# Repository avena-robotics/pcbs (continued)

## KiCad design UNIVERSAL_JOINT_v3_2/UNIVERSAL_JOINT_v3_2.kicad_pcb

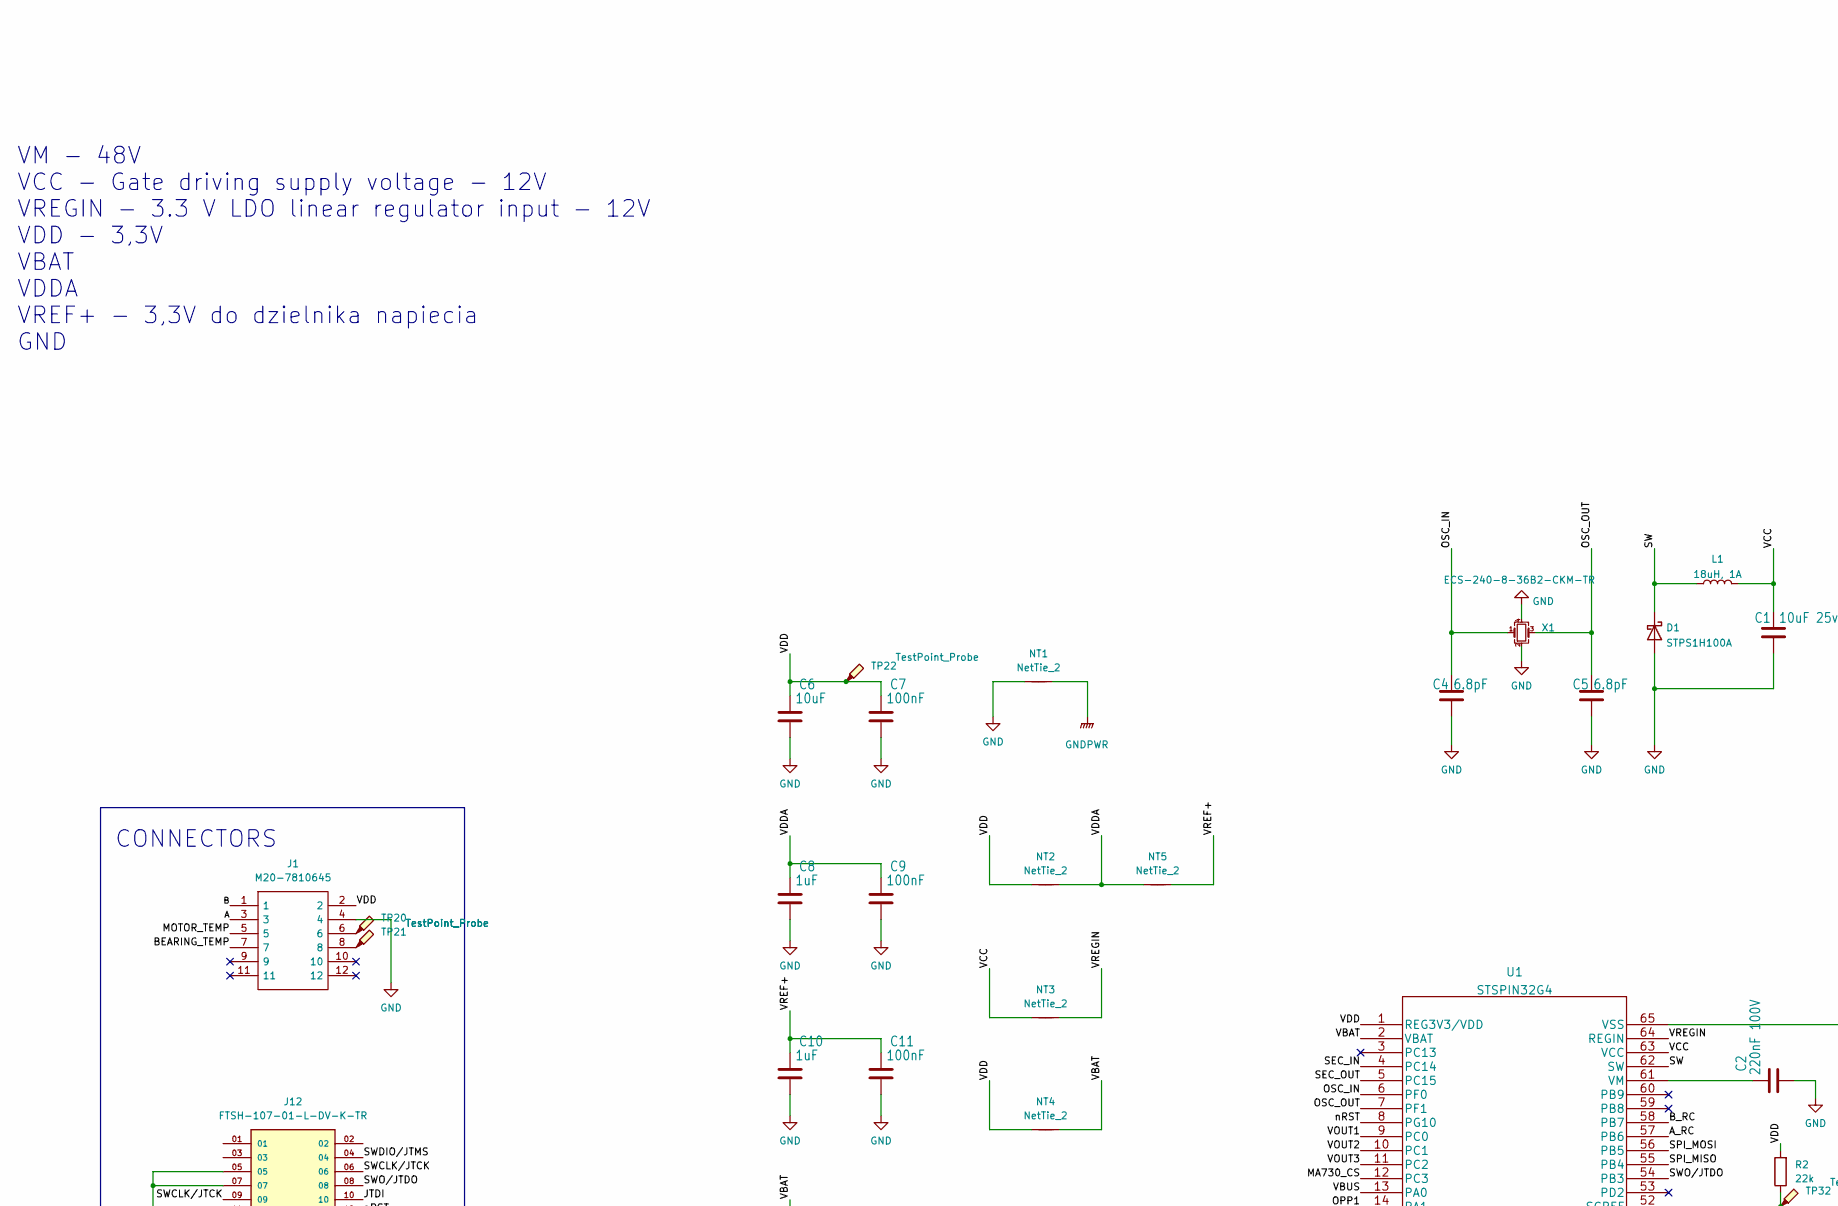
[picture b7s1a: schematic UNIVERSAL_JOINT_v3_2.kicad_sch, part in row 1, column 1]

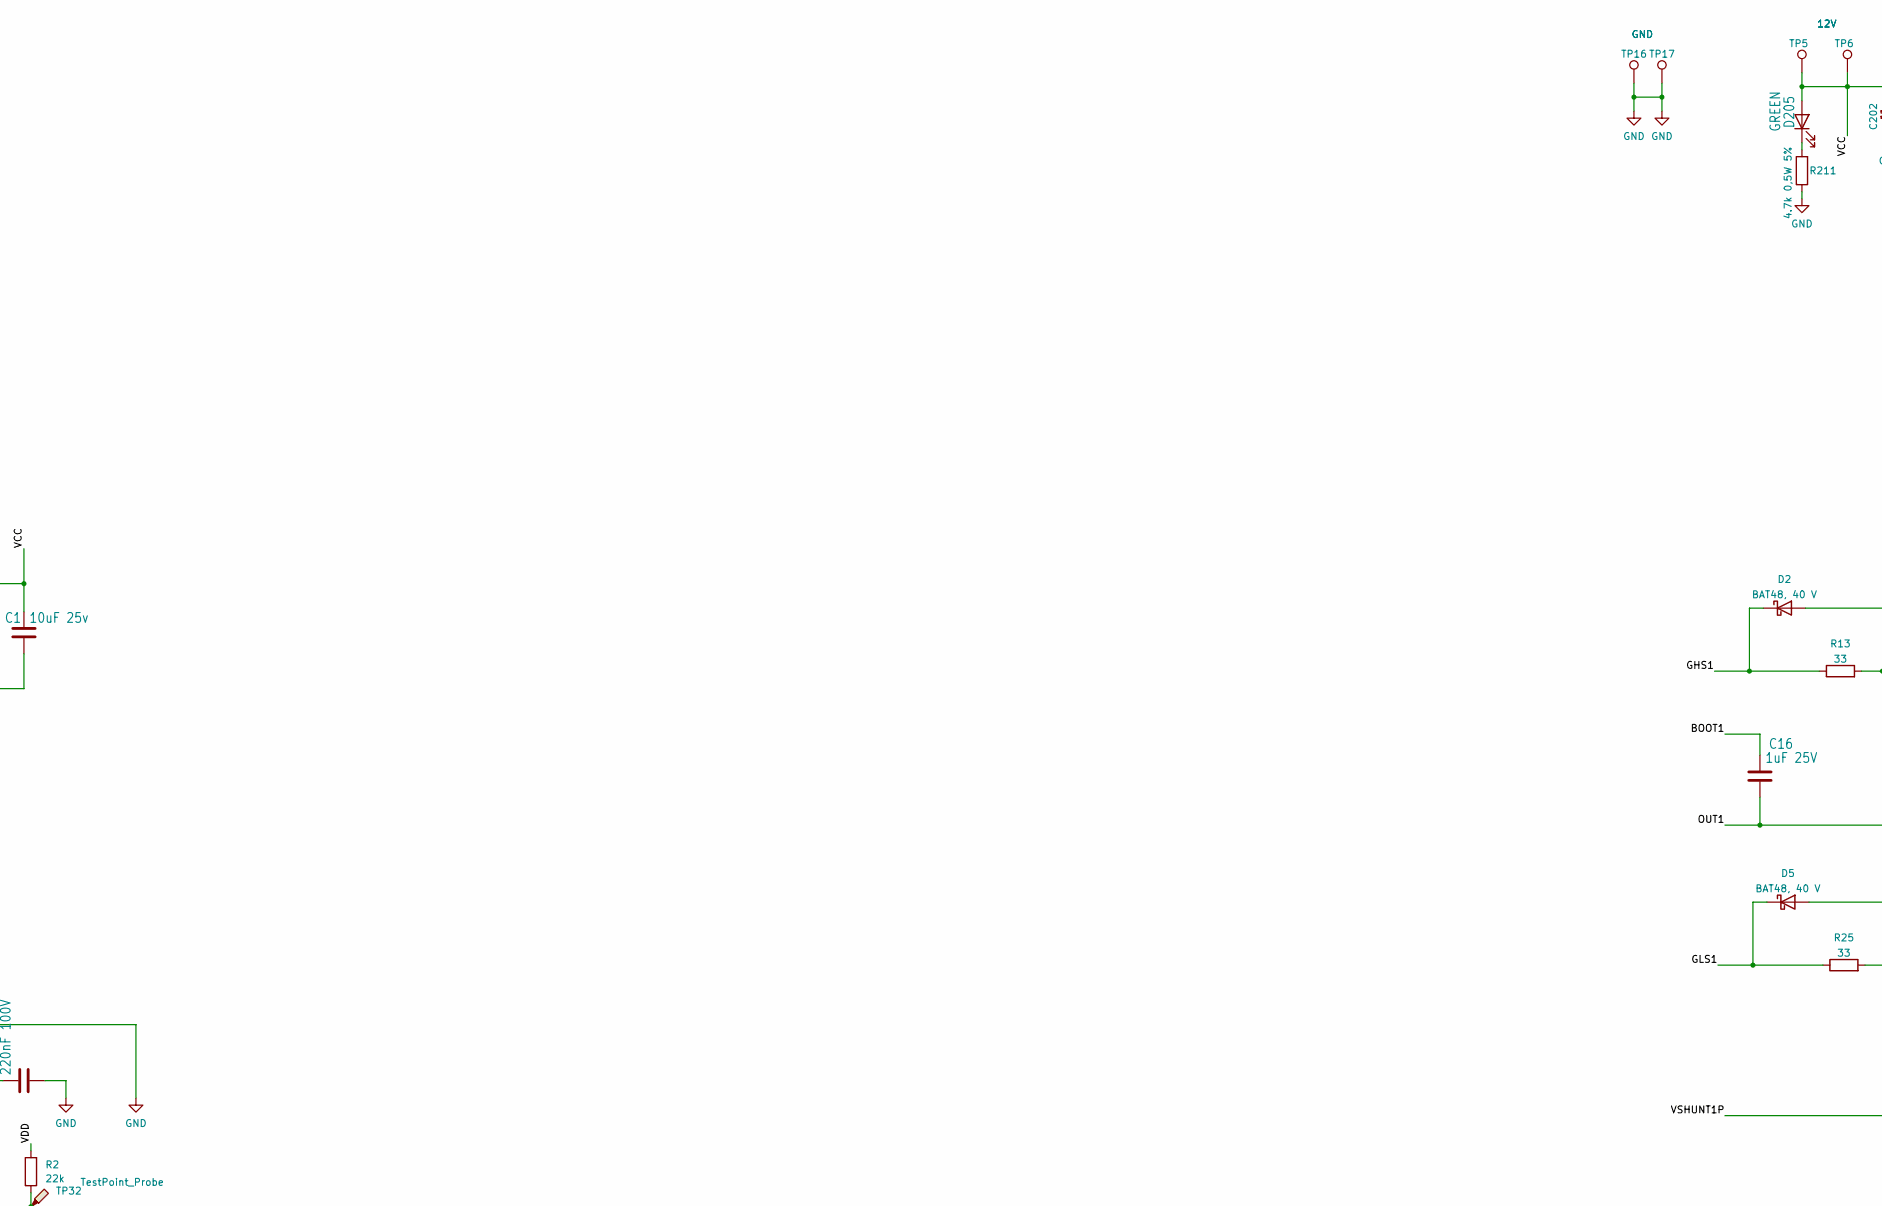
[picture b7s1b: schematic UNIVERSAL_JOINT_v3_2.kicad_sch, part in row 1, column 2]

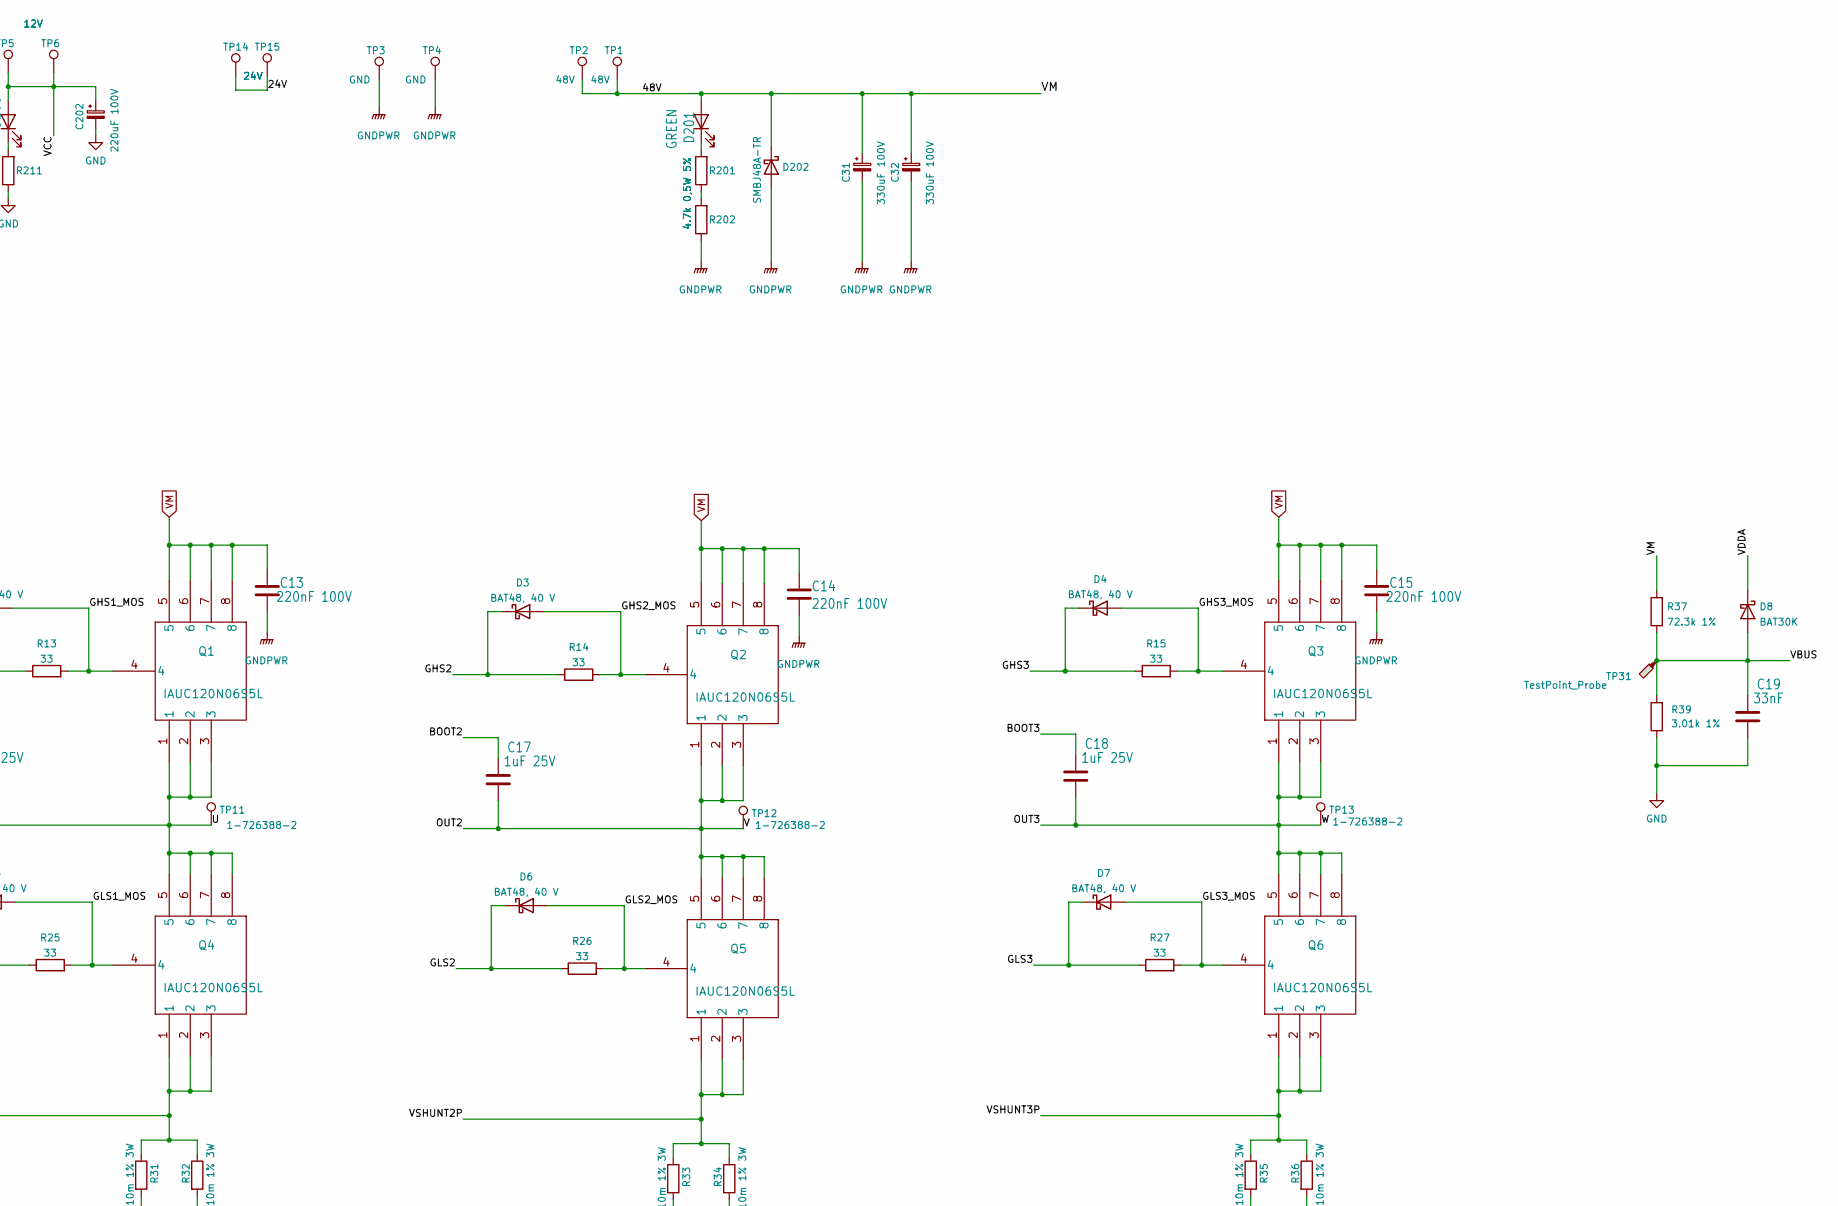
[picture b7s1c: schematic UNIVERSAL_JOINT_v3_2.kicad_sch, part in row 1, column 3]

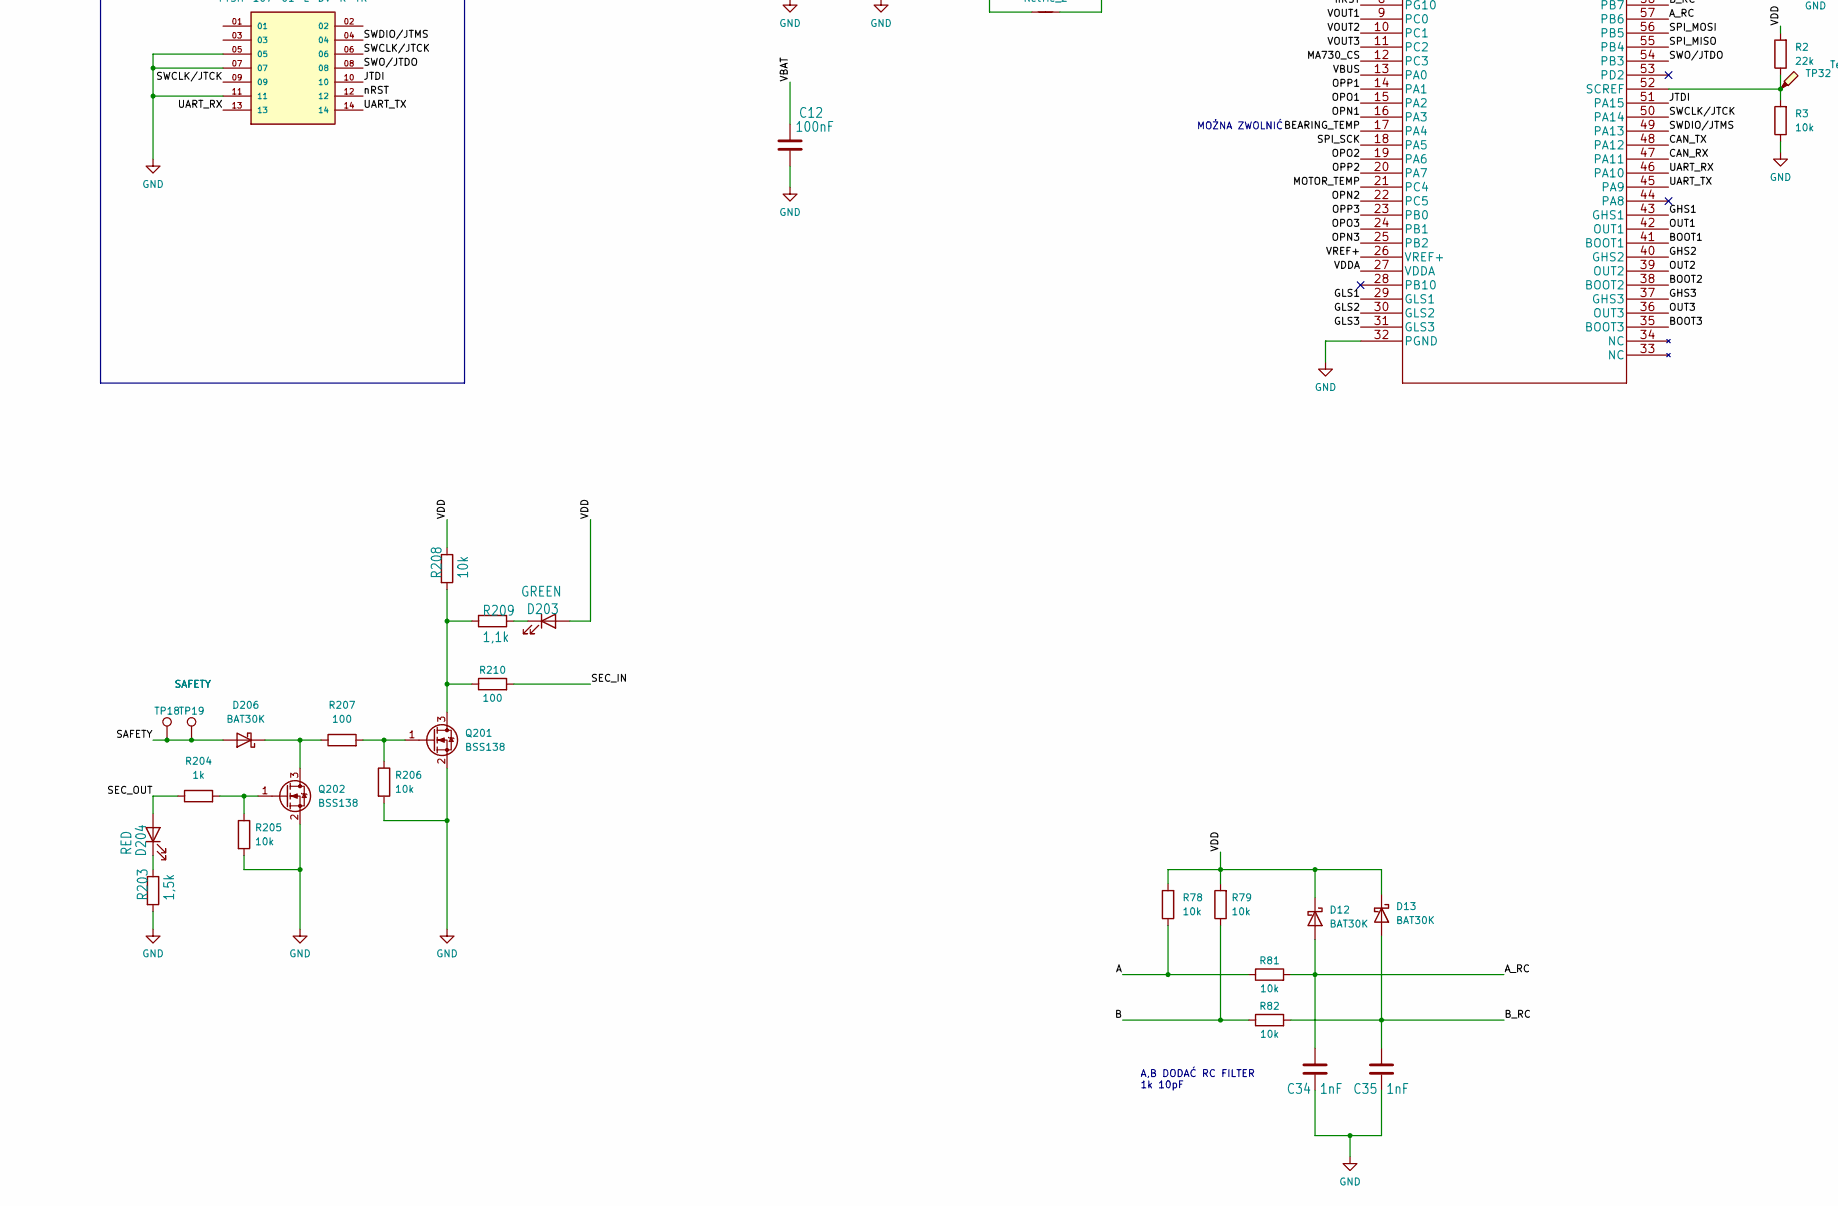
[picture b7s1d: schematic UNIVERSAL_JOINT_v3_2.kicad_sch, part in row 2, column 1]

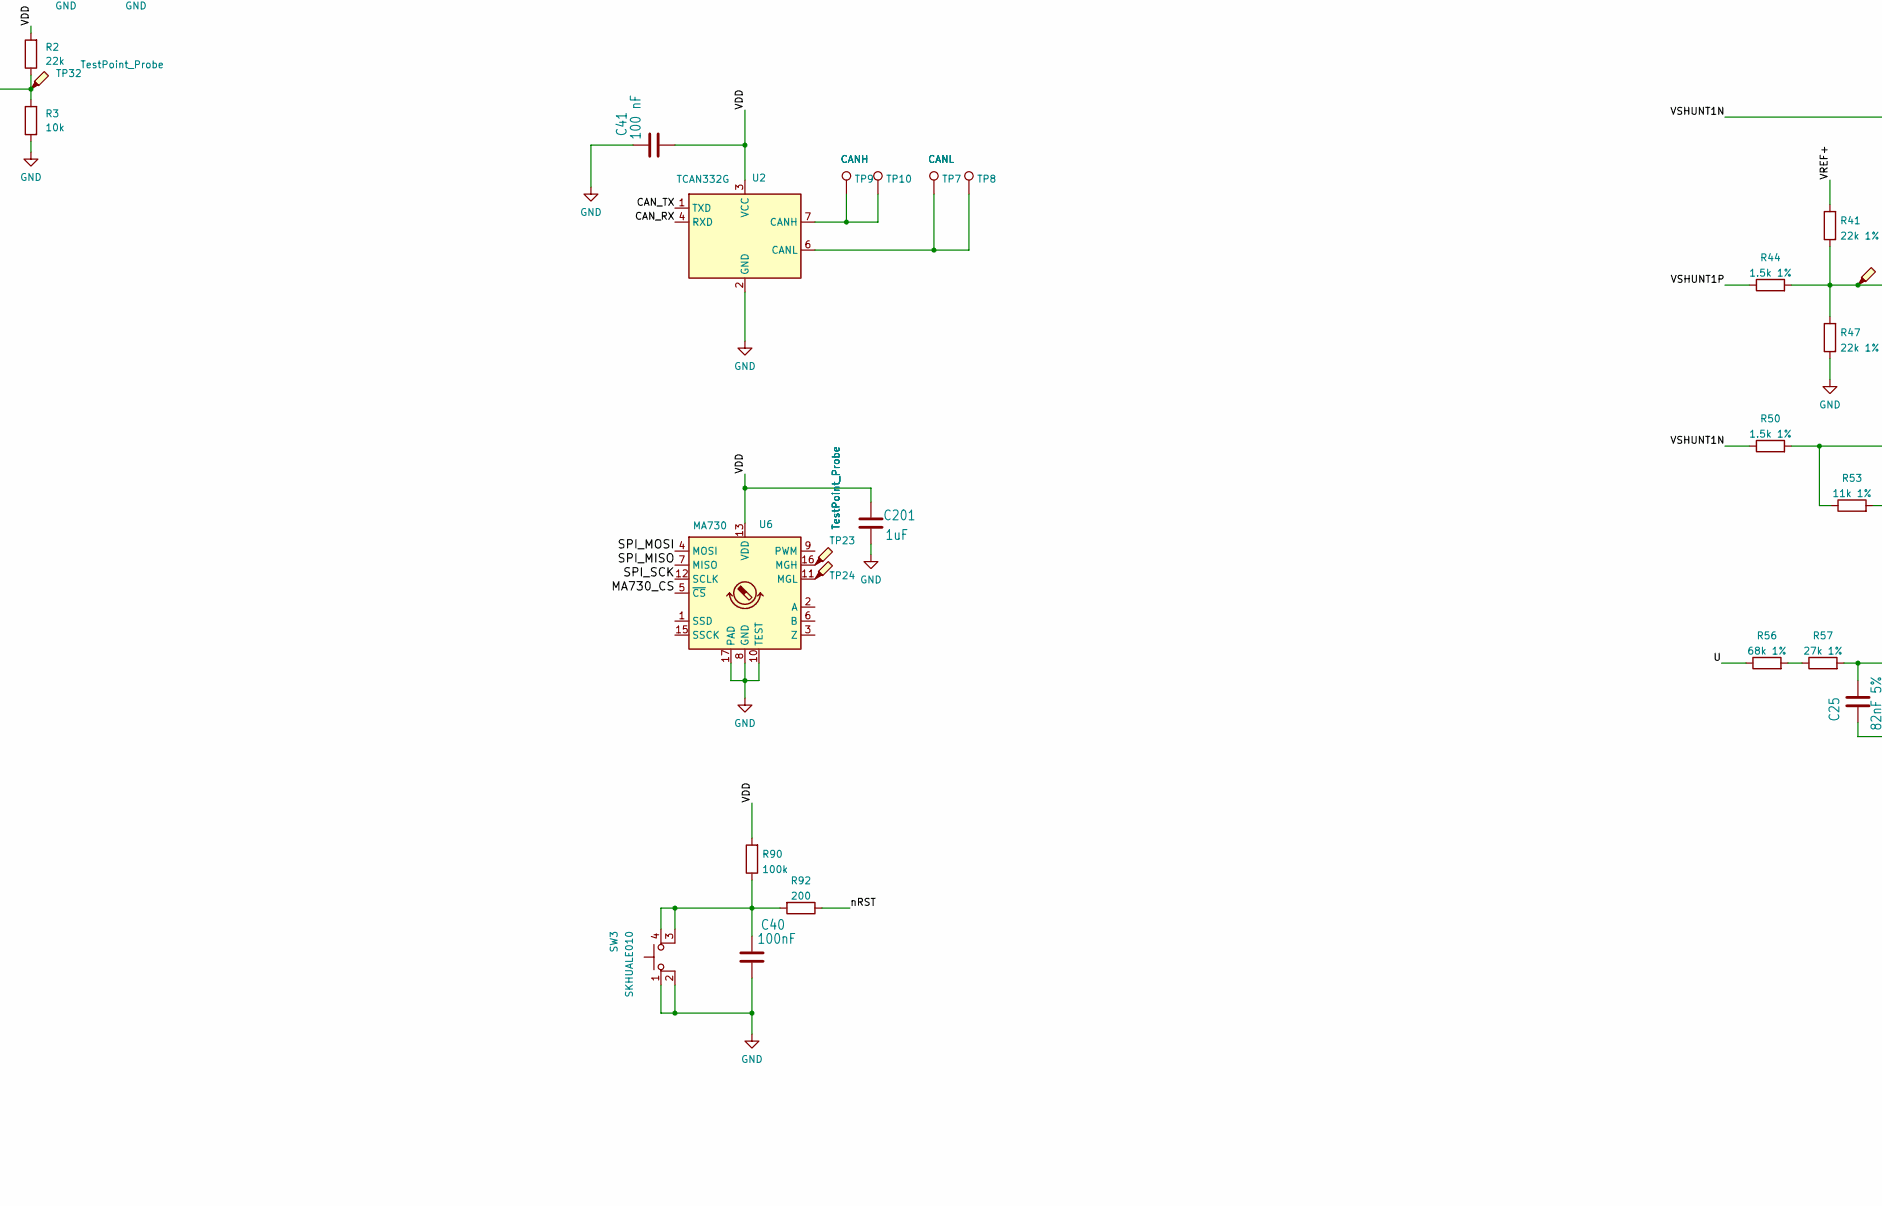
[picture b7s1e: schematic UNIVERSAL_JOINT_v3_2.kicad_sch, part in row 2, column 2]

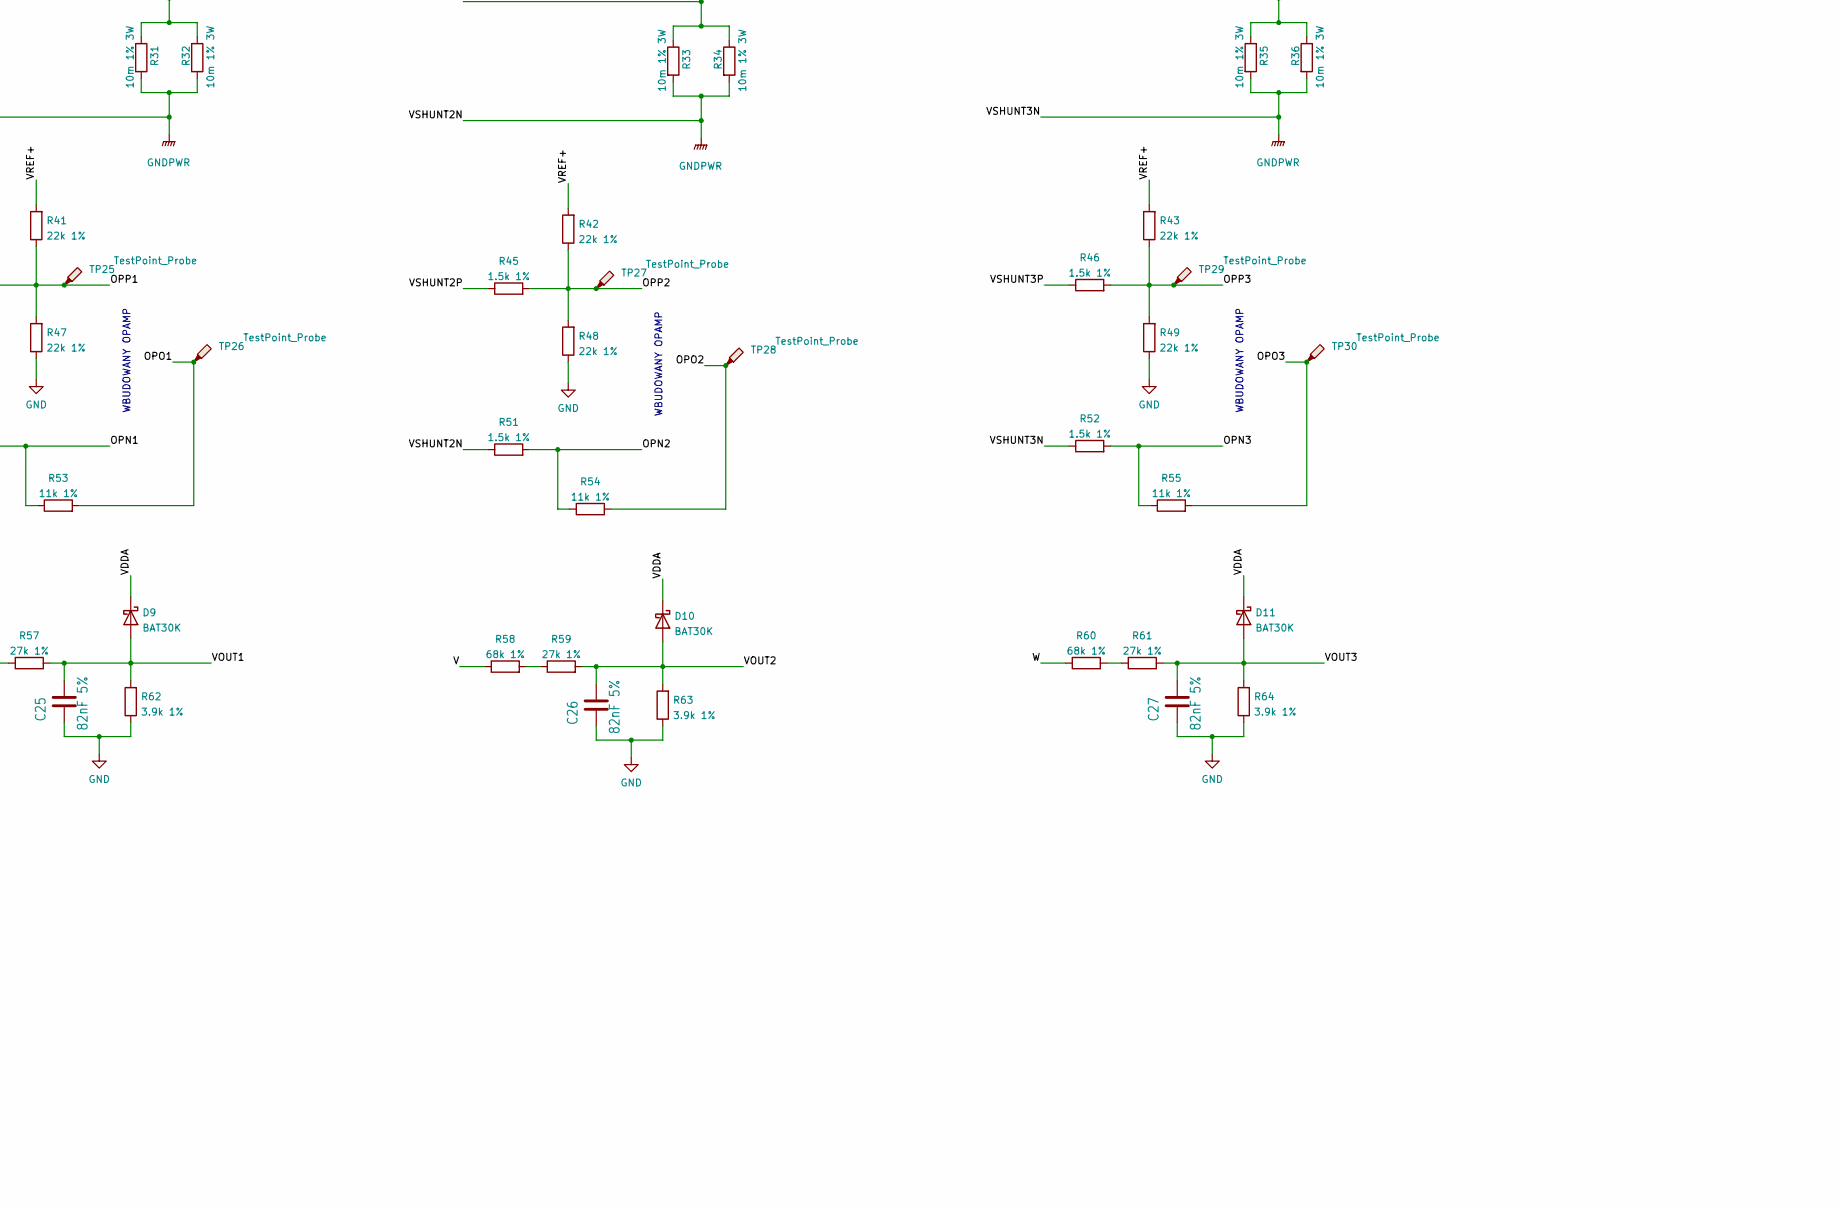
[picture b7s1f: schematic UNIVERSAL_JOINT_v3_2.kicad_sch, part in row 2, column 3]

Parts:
C1: 10uF 25v; C_0603_1608Metric_Pad1.08x0.95mm_HandSolder
C2, C13, C14, C15: 220nF 100V; C_0603_1608Metric_Pad1.08x0.95mm_HandSolder
C4, C5: 6.8pF; C_0603_1608Metric_Pad1.08x0.95mm_HandSolder
C6: 10uF; C_0603_1608Metric_Pad1.08x0.95mm_HandSolder
C7, C9, C11, C12, C40: 100nF; C_0603_1608Metric_Pad1.08x0.95mm_HandSolder
C8, C10, C201: 1uF; C_0603_1608Metric_Pad1.08x0.95mm_HandSolder
C16, C17, C18: 1uF 25V; C_0603_1608Metric_Pad1.08x0.95mm_HandSolder
C19: 33nF; C_0603_1608Metric_Pad1.08x0.95mm_HandSolder
C25, C26, C27: 82nF 5%; C_0603_1608Metric_Pad1.08x0.95mm_HandSolder
C31, C32: 330uF 100V; CP_Radial_D12.5mm_P5.00mm
C34, C35: 1nF; C_0603_1608Metric_Pad1.08x0.95mm_HandSolder
C41: 100 nF; C_0603_1608Metric_Pad1.08x0.95mm_HandSolder
C202: 220uF 100V; CP_Radial_D6.3mm_P2.50mm
D1: STPS1H100A; D_0603_1608Metric_Pad1.05x0.95mm_HandSolder
D2, D3, D4, D5, D6, D7: BAT48, 40 V; D_0603_1608Metric_Pad1.05x0.95mm_HandSolder
D8, D9, D10, D11, D12, D13, D206: BAT30K; D_0603_1608Metric_Pad1.05x0.95mm_HandSolder
D201, D203, D205: GREEN; D_0603_1608Metric_Pad1.05x0.95mm_HandSolder
D202: SMBJ48A-TR; D_0603_1608Metric_Pad1.05x0.95mm_HandSolder
D204: RED; D_0603_1608Metric_Pad1.05x0.95mm_HandSolder
J1: M20-7810645; Mouser Part Number 855-M20-7810645
J12: FTSH-107-01-L-DV-K-TR; SAMTEC_FTSH-107-01-L-DV-K-TR; PARTREV R
L1: 18uH, 1A; L_Wuerth_WE-PD2-Typ-MS
NT1, NT2, NT3, NT4, NT5: NetTie_2; NetTie-2_SMD_Pad0.5mm
Q1, Q2, Q3, Q4, Q5, Q6: IAUC120N06S5L; STL110N10F7
Q201, Q202: BSS138; SOT-23
R2: 22k; R_0603_1608Metric_Pad0.98x0.95mm_HandSolder
R3, R78, R79, R81, R82, R205, R206, R208: 10k; R_0603_1608Metric_Pad0.98x0.95mm_HandSolder
R13, R14, R15, R25, R26, R27: 33; R_0603_1608Metric_Pad0.98x0.95mm_HandSolder
R31, R32, R33, R34, R35, R36: 10m 1% 3W; R_2512_6332Metric_Pad1.40x3.35mm_HandSolder
R37: 72.3k 1%; R_0603_1608Metric_Pad0.98x0.95mm_HandSolder
R39: 3.01k 1%; R_0603_1608Metric_Pad0.98x0.95mm_HandSolder
R41, R42, R43, R47, R48, R49: 22k 1%; R_0603_1608Metric_Pad0.98x0.95mm_HandSolder
R44, R45, R46, R50, R51, R52: 1.5k 1%; R_0603_1608Metric_Pad0.98x0.95mm_HandSolder
R53, R54, R55: 11k 1%; R_0603_1608Metric_Pad0.98x0.95mm_HandSolder
R56, R58, R60: 68k 1%; R_0603_1608Metric_Pad0.98x0.95mm_HandSolder
R57, R59, R61: 27k 1%; R_0603_1608Metric_Pad0.98x0.95mm_HandSolder
R62, R63, R64: 3.9k 1%; R_0603_1608Metric_Pad0.98x0.95mm_HandSolder
R90: 100k; R_0603_1608Metric_Pad0.98x0.95mm_HandSolder
R92: 200; R_0603_1608Metric_Pad0.98x0.95mm_HandSolder
R201, R202, R211: 4.7k 0,5W 5%; R_0603_1608Metric_Pad0.98x0.95mm_HandSolder
R203: 1,5k; R_0603_1608Metric_Pad0.98x0.95mm_HandSolder
R204: 1k; R_0603_1608Metric_Pad0.98x0.95mm_HandSolder
R207, R210: 100; R_0603_1608Metric_Pad0.98x0.95mm_HandSolder
R209: 1,1k; R_0603_1608Metric_Pad0.98x0.95mm_HandSolder
SW3: SKHUALE010
TP1, TP2: 48V; 1-726388-2
TP3, TP4: GND; 1-726388-2
TP5, TP6: 12V; 61-2348-11_0030
TP7, TP8: CANL; KEYS_3544
TP9, TP10: CANH; 61-2348-11_0030
TP11, TP12, TP13: 1-726388-2; 61-2348-11_0030
TP14, TP15: 24V; KEYS_3578
TP16, TP17: GND; 61-2348-11_0030
TP18, TP19: SAFETY; KEYS_3544
TP20, TP21, TP22, TP23, TP24, TP25, TP26, TP27, TP28, TP29, TP30, TP31, TP32: TestPoint_Probe; TestPoint_Pad_D1.0mm
U1: STSPIN32G4
U2: TCAN332G; SO-8_3.9x4.9mm_P1.27mm
U6: MA730; MA730GQ-Z
X1: ECS-240-8-36B2-CKM-TR; ECX-2236B2

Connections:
/24V: TP14.1, TP15.1
/A: J1.3, R78.1, R81.1
/A_RC: C34.1, D12.2 (A), R81.2, U1.57 (PB6)
/B: J1.1, R79.1, R82.1
/BEARING_TEMP: J1.7, U1.17 (PA4)
/BOOT1: C16.2, U1.41 (BOOT1)
/BOOT2: C17.2, U1.38 (BOOT2)
/BOOT3: C18.2, U1.35 (BOOT3)
/B_RC: C35.1, D13.2 (A), R82.2, U1.58 (PB7)
/CAN_RX: U1.47 (PA11), U2.4 (RXD)
/CAN_TX: U1.48 (PA12), U2.1 (TXD)
/GHS1: D2.1 (K), R13.1, U1.43 (GHS1)
/GHS1_MOS: D2.2 (A), Q1.4, R13.2
/GHS2: D3.1 (K), R14.1, U1.40 (GHS2)
/GHS2_MOS: D3.2 (A), Q2.4, R14.2
/GHS3: D4.1 (K), R15.1, U1.37 (GHS3)
/GHS3_MOS: D4.2 (A), Q3.4, R15.2
/GLS1: D5.1 (K), R25.1, U1.29 (GLS1)
/GLS1_MOS: D5.2 (A), Q4.4, R25.2
/GLS2: D6.1 (K), R26.1, U1.30 (GLS2)
/GLS2_MOS: D6.2 (A), Q5.4, R26.2
/GLS3: D7.1 (K), R27.1, U1.31 (GLS3)
/GLS3_MOS: D7.2 (A), Q6.4, R27.2
/JTDI: J12.10, U1.51 (PA15)
/MA730_CS: U1.12 (PC3), U6.5 (~CS)
/MOTOR_TEMP: J1.5, U1.21 (PC4)
/OPN1: R50.2, R53.1, U1.16 (PA3)
/OPN2: R51.2, R54.1, U1.22 (PC5)
/OPN3: R52.2, R55.1, U1.25 (PB2)
/OPO1: R53.2, TP26.1, U1.15 (PA2)
/OPO2: R54.2, TP28.1, U1.19 (PA6)
/OPO3: R55.2, TP30.1, U1.24 (PB1)
/OPP1: R41.1, R44.2, R47.2, TP25.1, U1.14 (PA1)
/OPP2: R42.1, R45.2, R48.2, TP27.1, U1.20 (PA7)
/OPP3: R43.1, R46.2, R49.2, TP29.1, U1.23 (PB0)
/OSC_IN: C4.2, U1.6 (PF0), X1.1
/OSC_OUT: C5.2, U1.7 (PF1), X1.3
/OUT1: C16.1, Q1.1, Q1.2, Q1.3, Q4.5, Q4.6, Q4.7, Q4.8, R56.1, TP11.1, U1.42 (OUT1)
/OUT2: C17.1, Q2.1, Q2.2, Q2.3, Q5.5, Q5.6, Q5.7, Q5.8, R58.1, TP12.1, U1.39 (OUT2)
/OUT3: C18.1, Q3.1, Q3.2, Q3.3, Q6.5, Q6.6, Q6.7, Q6.8, R60.1, TP13.1, U1.36 (OUT3)
/SAFETY: D206.2 (A), TP18.1, TP19.1
/SEC_IN: R210.2, U1.4 (PC14)
/SEC_OUT: D204.2 (A), R204.1, U1.5 (PC15)
/SPI_MISO: U1.55 (PB4), U6.7 (MISO)
/SPI_MOSI: U1.56 (PB5), U6.4 (MOSI)
/SPI_SCK: U1.18 (PA5), U6.12 (SCLK)
/SW: D1.1 (K), L1.1, U1.62 (SW)
/SWCLK/JTCK: J12.06, J12.09, U1.50 (PA14)
/SWDIO/JTMS: J12.04, U1.49 (PA13)
/SWO/JTDO: J12.08, U1.54 (PB3)
/UART_RX: J12.13, U1.46 (PA10)
/UART_TX: J12.14, U1.45 (PA9)
/VBAT: C12.2, NT4.2, U1.2 (VBAT)
/VBUS: C19.2, D8.2 (A), R37.1, R39.2, TP31.1, U1.13 (PA0)
/VCC: C1.2, C202.1, D205.2 (A), L1.2, NT3.1, TP5.1, TP6.1, U1.63 (VCC)
/VDD: C6.2, C7.2, C41.1, C201.2, D12.1 (K), D13.1 (K), D203.2 (A), J1.2, NT2.1, NT4.1, R2.2, R78.2, R79.2, R90.2, R208.1, TP22.1, U1.1 (REG3V3/VDD), U2.3 (VCC), U6.13 (VDD)
/VDDA: C8.2, C9.2, D8.1 (K), D9.1 (K), D10.1 (K), D11.1 (K), NT2.2, NT5.1, U1.27 (VDDA)
/VOUT1: C25.1, D9.2 (A), R57.2, R62.2, U1.9 (PC0)
/VOUT2: C26.1, D10.2 (A), R59.2, R63.2, U1.10 (PC1)
/VOUT3: C27.1, D11.2 (A), R61.2, R64.2, U1.11 (PC2)
/VREF+: C10.2, C11.2, NT5.2, R41.2, R42.2, R43.2, U1.26 (VREF+)
/VREGIN: NT3.2, U1.64 (REGIN)
/VSHUNT1P: Q4.1, Q4.2, Q4.3, R31.1, R32.1, R44.1
/VSHUNT2P: Q5.1, Q5.2, Q5.3, R33.1, R34.1, R45.1
/VSHUNT3P: Q6.1, Q6.2, Q6.3, R35.1, R36.1, R46.1
/nRST: J12.12, R92.1, U1.8 (PG10)
GND: C1.1, C2.1, C4.1, C5.1, C6.1, C7.1, C8.1, C9.1, C10.1, C11.1, C12.1, C19.1, C25.2, C26.2, C27.2, C34.2, C35.2, C40.1, C41.2, C201.1, C202.2, D1.2 (A), J1.4, J12.05, J12.07, J12.11, NT1.1, Q201.2 (S), Q202.2 (S), R3.1, R39.1, R47.1, R48.1, R49.1, R62.1, R63.1, R64.1, R203.2, R205.2, R206.2, R211.1, SW3.1, SW3.2, TP16.1, TP17.1, U1.32 (PGND), U1.65 (VSS), U2.2 (GND), U6.8 (GND), U6.10 (TEST), U6.17 (PAD), X1.2, X1.4
GNDPWR: C13.1, C14.1, C15.1, C31.2, C32.2, D202.2 (A), NT1.2, R31.2, R32.2, R33.2, R34.2, R35.2, R36.2, R50.1, R51.1, R52.1, R202.1, TP3.1, TP4.1
unnamed: C2.2, U1.61 (VM)
unnamed: C40.2, R90.1, R92.2, SW3.3 (K), SW3.4 (A)
unnamed: D201.1 (K), R201.2
unnamed: D203.1 (K), R209.1
unnamed: D204.1 (K), R203.1
unnamed: D205.1 (K), R211.2
unnamed: D206.1 (K), Q202.3 (D), R207.1
unnamed: J1.6, TP20.1
unnamed: J1.8, TP21.1
unnamed: Q201.1 (G), R206.1, R207.2
unnamed: Q201.3 (D), R208.2, R209.2, R210.1
unnamed: Q202.1 (G), R204.2, R205.1
unnamed: R2.1, R3.2, TP32.1, U1.52 (SCREF)
unnamed: R56.2, R57.1
unnamed: R58.2, R59.1
unnamed: R60.2, R61.1
unnamed: R201.1, R202.2
unnamed: TP7.1, TP8.1, U2.6 (CANL)
unnamed: TP9.1, TP10.1, U2.7 (CANH)
unnamed: TP23.1, U6.16 (MGH)
unnamed: TP24.1, U6.11 (MGL)
VM: C13.2, C14.2, C15.2, C31.1, C32.1, D201.2 (A), D202.1 (K), Q1.5, Q1.6, Q1.7, Q1.8, Q2.5, Q2.6, Q2.7, Q2.8, Q3.5, Q3.6, Q3.7, Q3.8, R37.2, TP1.1, TP2.1

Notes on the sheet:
VM - 48V VCC - Gate driving supply voltage - 12V VREGIN - 3.3 V LDO linear regulator input - 12V VDD - 3,3V VBAT VDDA VREF+ - 3,3V do dzielnika napiecia GND
CONNECTORS
WBUDOWANY OPAMP
A,B DODAĆ RC FILTER 1k 10pF
MOŻNA ZWOLNIĆ

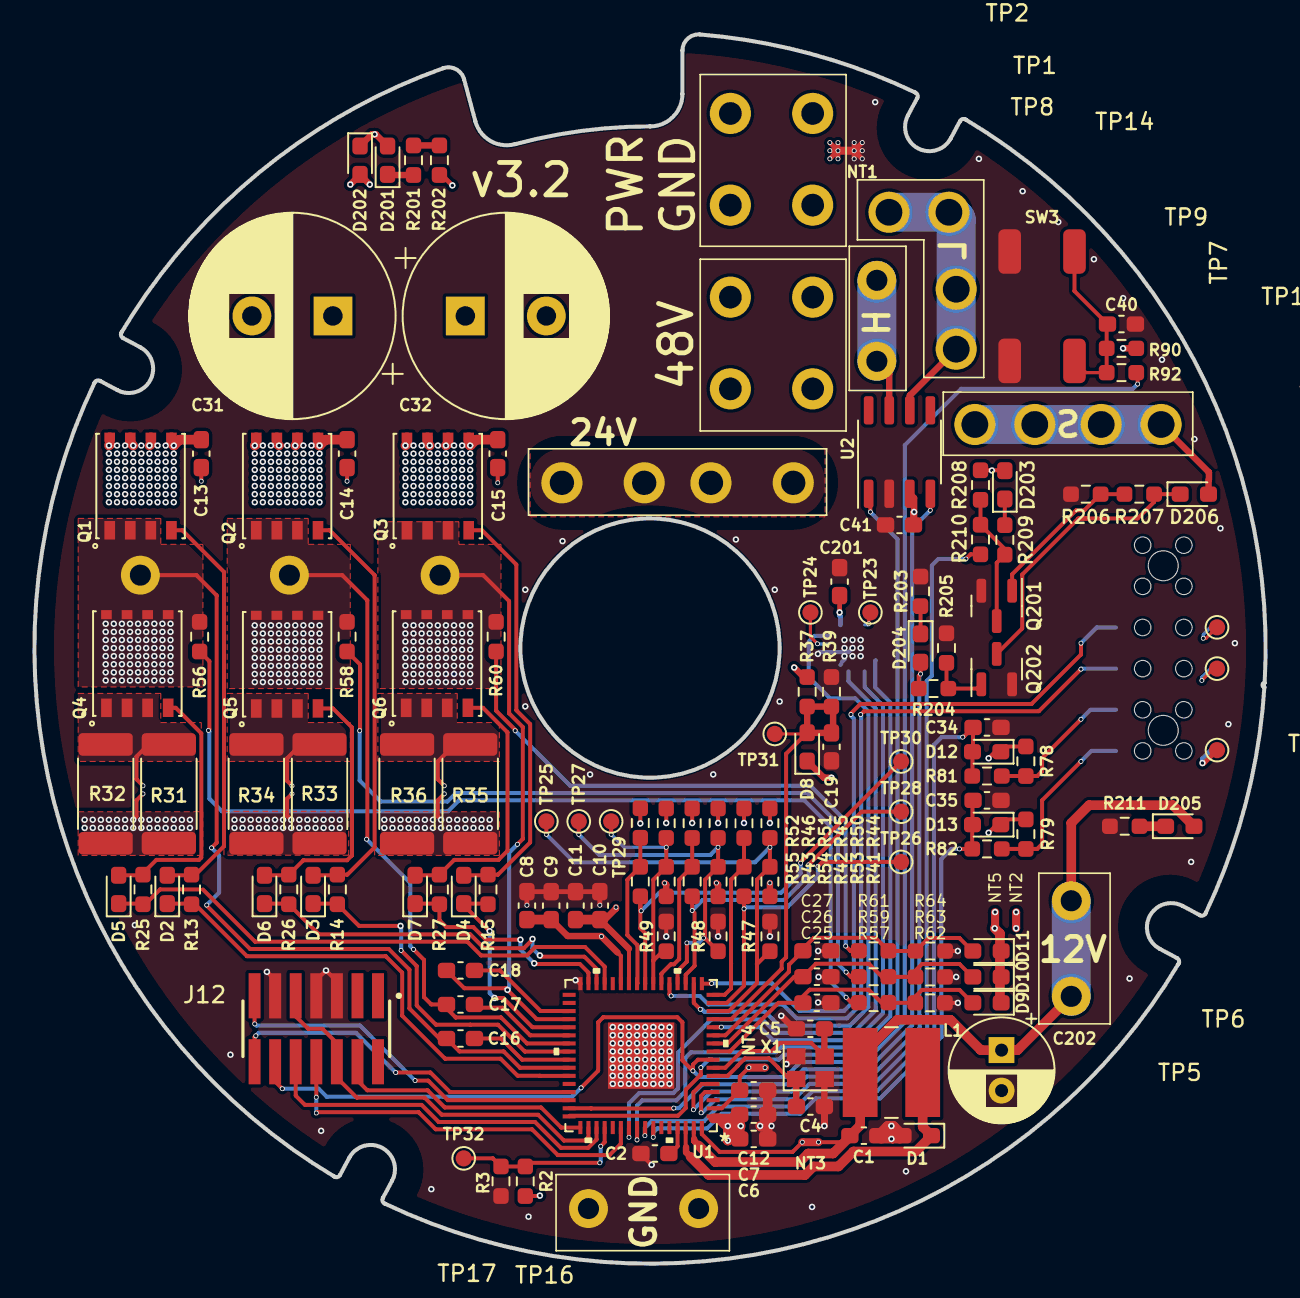
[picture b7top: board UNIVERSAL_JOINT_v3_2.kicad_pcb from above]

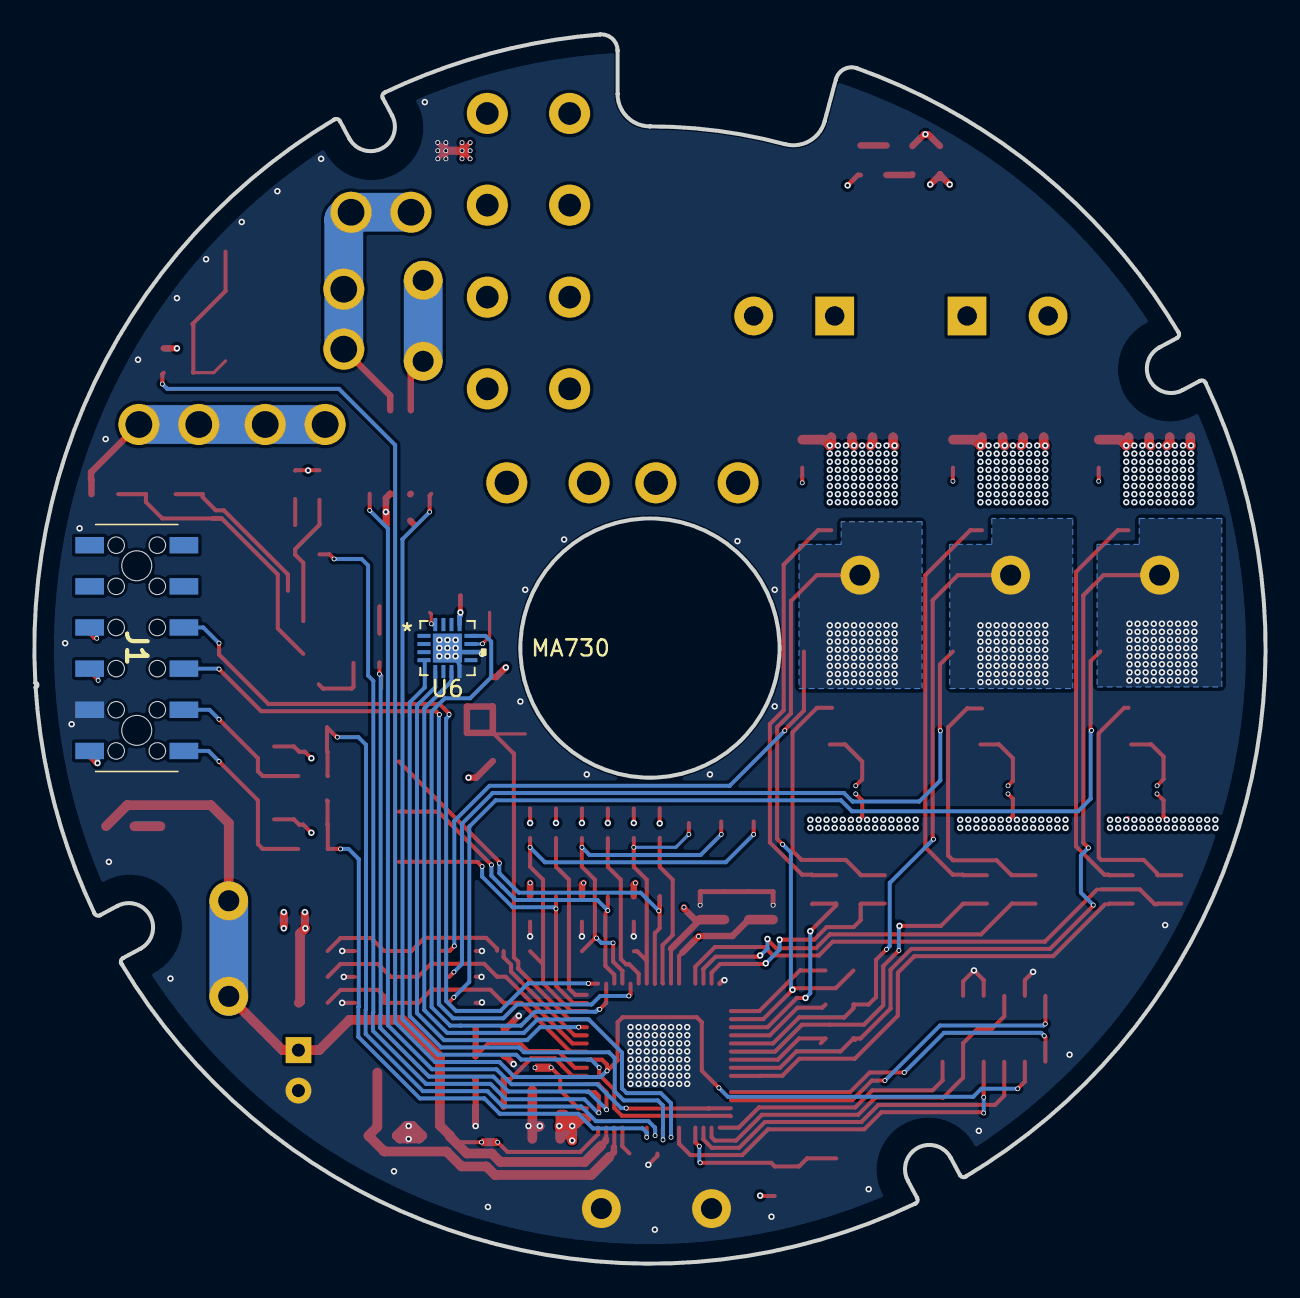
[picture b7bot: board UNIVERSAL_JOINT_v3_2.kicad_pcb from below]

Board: 4 copper layers, 76.0 x 75.9 mm, 158 parts (2 on the bottom side), 90 nets.

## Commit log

2021-11-14 migration from gitlab
2021-11-19 remove universal joint 2.2.1
2021-11-30 UJ 3.1 IR 0.3 TACTILE 2.1
2021-11-30 UH 2.8 RI80
2021-12-08 add gripper and so on
2021-12-10 UJ 2.2 remove brake resistor
2021-12-13 update NM parts
2021-12-14 tactile 2.1
2021-12-17 update UJ 3.1 NM values
2022-01-12 MASTER UPDATE
2022-01-12 MASTER UPDATE v2
2022-02-07 update to newest
2022-03-01 update descriptions
2022-05-02 udpate
2022-06-06 Iboms addded
2022-06-21 UJ34
2022-07-06 new UJ 3.5
2022-07-13 UJ 3.5 - draft
